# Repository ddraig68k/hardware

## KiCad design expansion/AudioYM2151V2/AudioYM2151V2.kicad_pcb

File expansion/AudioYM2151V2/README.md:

# YM2151 V2 Sound Card

This second version of the [YM2151 Sound Card](/YM2151-Sound/) extends the capabilites of the original. In addition to the YM2151, two Oki MSM6258 chips for dual ADPCM audio channels.

The 68008 memory map
| Device | Start Address | End Address |
|-|-|-|
| Static Ram    | 0x000000 | 0x07FFFF |
| ROM           | 0x100000 | 0x107FFF |
| STATUS_LATCH	| 0x200000 | 0x200000 |
| REG_LATCH	    | 0x200001 | 0x200001 |
| DATA_LATCH	| 0x200002 | 0x200002 |
| DUART	        | 0x200100 | 0x2001FF |
| YM2151	    | 0x200200 | 0x2002FF |
| MSM6295 1	    | 0x200300 | 0x2003FF |
| MSM6295 2	    | 0x200400 | 0x2004FF |

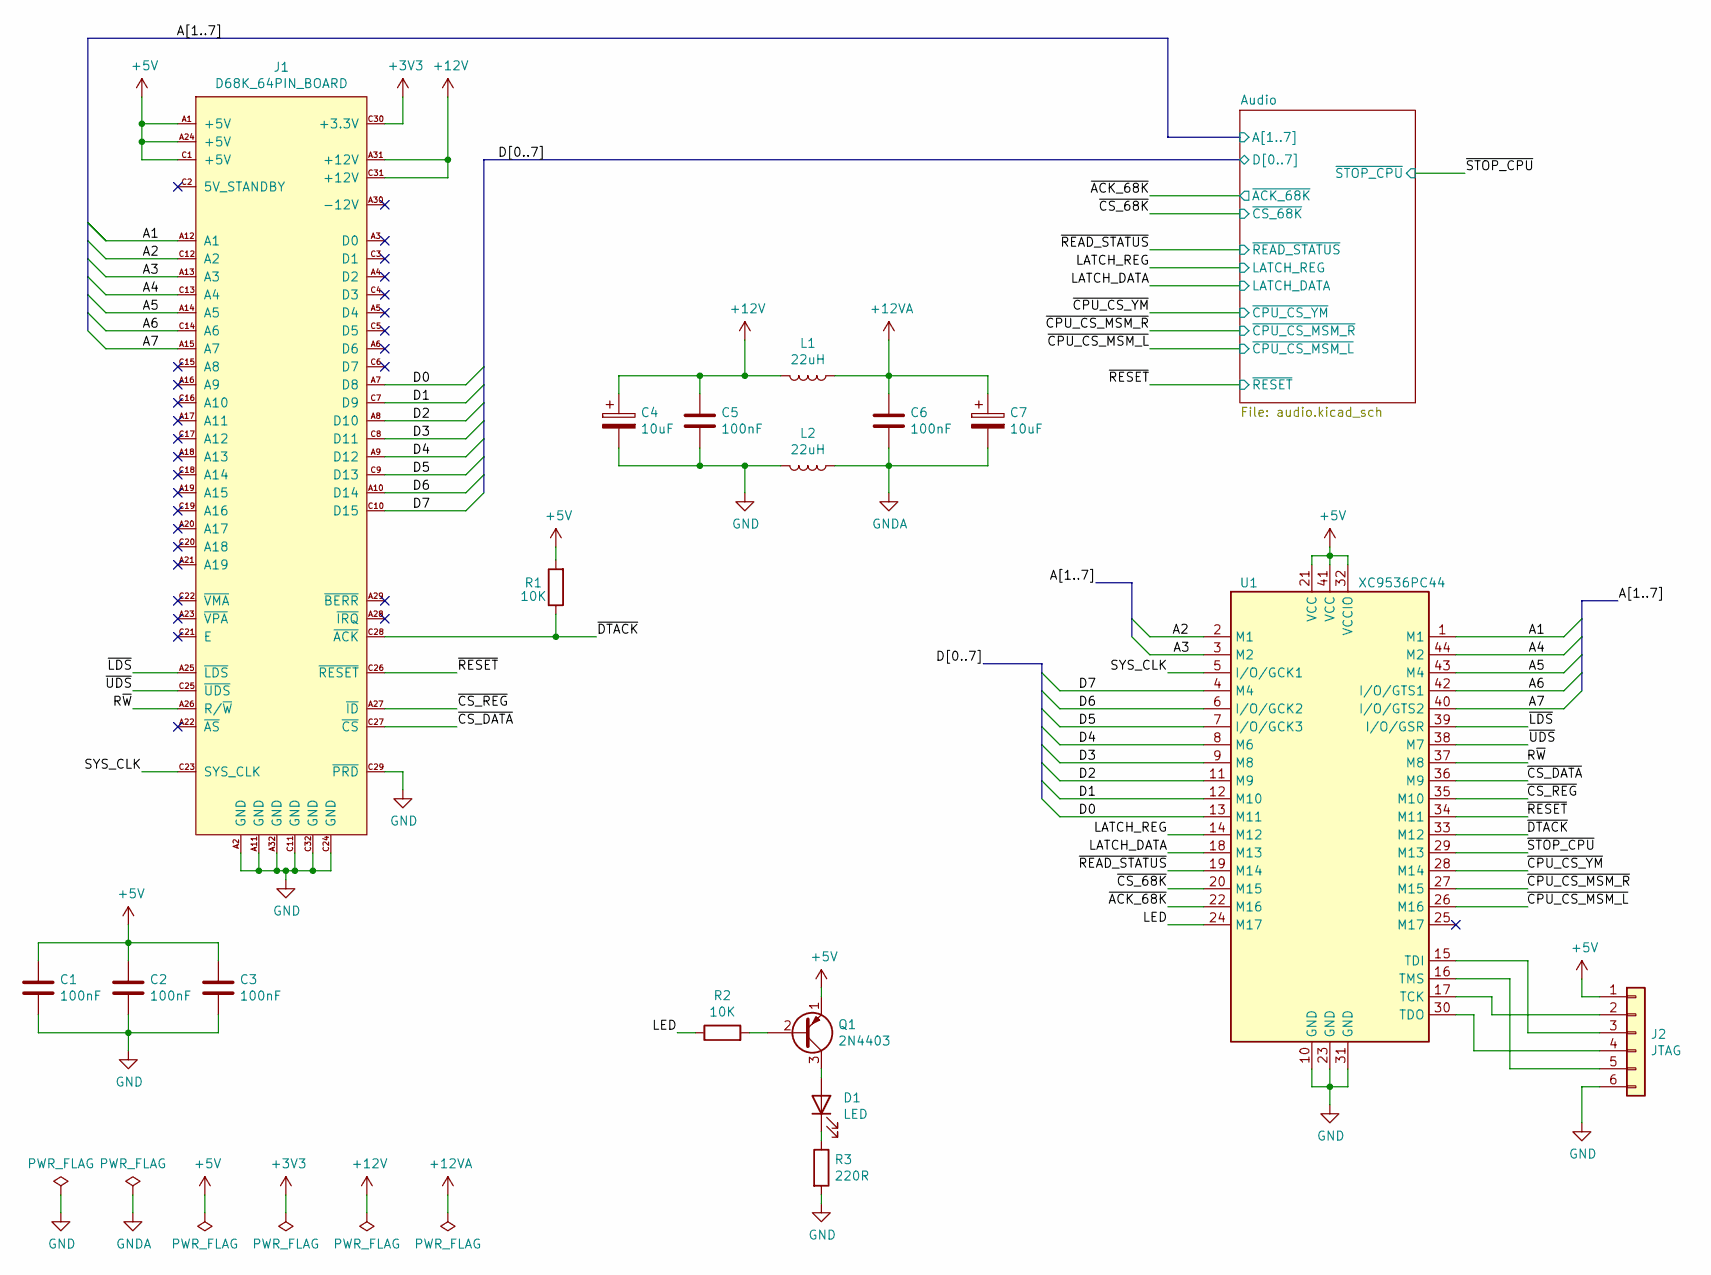
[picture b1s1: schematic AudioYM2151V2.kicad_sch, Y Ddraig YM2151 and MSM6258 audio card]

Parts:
C1, C2, C3, C5, C6: 100nF; C_Disc_D5.0mm_W2.5mm_P2.50mm
C4, C7: 10uF; CP_Radial_D5.0mm_P2.50mm
D1: LED; LED_D5.0mm
J1: D68K_64PIN_BOARD; DIN41612_C_2x32_Male_Horizontal_THT
J2: JTAG; PinHeader_1x06_P2.54mm_Vertical
L1, L2: 22uH; L_Radial_D8.7mm_P5.00mm_Fastron_07HCP
Q1: 2N4403; TO-92
R1, R2: 10K; R_Axial_DIN0207_L6.3mm_D2.5mm_P10.16mm_Horizontal
R3: 220R; R_Axial_DIN0207_L6.3mm_D2.5mm_P10.16mm_Horizontal
U1: XC9536PC44; PLCC-44_THT-Socket

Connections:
+3V3: J1.C30 (+3.3V)
+12V: C4.1, C5.1, J1.A31 (+12V), J1.C31 (+12V), L1.2
+12VA: C6.1, C7.1, L1.1; also elsewhere on the board
/A1: J1.A12 (A1), U1.1 (M1); also elsewhere on the board
/A2: J1.C12 (A2), U1.2 (M1); also elsewhere on the board
/A3: J1.A13 (A3), U1.3 (M2); also elsewhere on the board
/A4: J1.C13 (A4), U1.44 (M2); also elsewhere on the board
/A5: J1.A14 (A5), U1.43 (M4); also elsewhere on the board
/A6: J1.C14 (A6), U1.42 (I/O/GTS1); also elsewhere on the board
/A7: J1.A15 (A7), U1.40 (I/O/GTS2)
/D0: J1.A7 (D8), U1.13 (M11); also elsewhere on the board
/D1: J1.C7 (D9), U1.12 (M10); also elsewhere on the board
/D2: J1.A8 (D10), U1.11 (M9); also elsewhere on the board
/D3: J1.C8 (D11), U1.9 (M8); also elsewhere on the board
/D4: J1.A9 (D12), U1.8 (M6); also elsewhere on the board
/D5: J1.C9 (D13), U1.7 (I/O/GCK3); also elsewhere on the board
/D6: J1.A10 (D14), U1.6 (I/O/GCK2); also elsewhere on the board
/D7: J1.C10 (D15), U1.4 (M4); also elsewhere on the board
/LATCH_DATA: U1.18 (M13); also elsewhere on the board
/LATCH_REG: U1.14 (M12); also elsewhere on the board
/R~W: J1.A26 (R/~W), U1.37 (M8)
/SYS_CLK: J1.C23 (SYS_CLK), U1.5 (I/O/GCK1)
/~ACK_68K: U1.22 (M16); also elsewhere on the board
/~CPU_CS_MSM_L: U1.26 (M16); also elsewhere on the board
/~CPU_CS_MSM_R: U1.27 (M15); also elsewhere on the board
/~CPU_CS_YM: U1.28 (M14); also elsewhere on the board
/~CS_68K: U1.20 (M15); also elsewhere on the board
/~CS_DATA: J1.C27 (~CS), U1.36 (M9)
/~CS_REG: J1.A27 (~ID), U1.35 (M10)
/~DTACK: J1.C28 (~ACK), R1.1, U1.33 (M12)
/~LDS: J1.A25 (~LDS), U1.39 (I/O/GSR)
/~READ_STATUS: U1.19 (M14); also elsewhere on the board
/~RESET: J1.C26 (~RESET), U1.34 (M11); also elsewhere on the board
/~STOP_CPU: U1.29 (M13); also elsewhere on the board
/~UDS: J1.C25 (~UDS), U1.38 (M7)
GND: C1.2, C2.2, C3.2, C4.2, C5.2, J1.A2 (GND), J1.A11 (GND), J1.A32 (GND), J1.C11 (GND), J1.C24 (GND), J1.C29 (~PRD), J1.C32 (GND), J2.6, L2.2, R3.2, U1.10 (GND), U1.23 (GND), U1.31 (GND); also elsewhere on the board
GNDA: C6.2, C7.2, L2.1; also elsewhere on the board
unnamed: J2.2, U1.17 (TCK)
unnamed: J2.3, U1.15 (TDI)
unnamed: J2.4, U1.30 (TDO)
unnamed: J2.5, U1.16 (TMS)

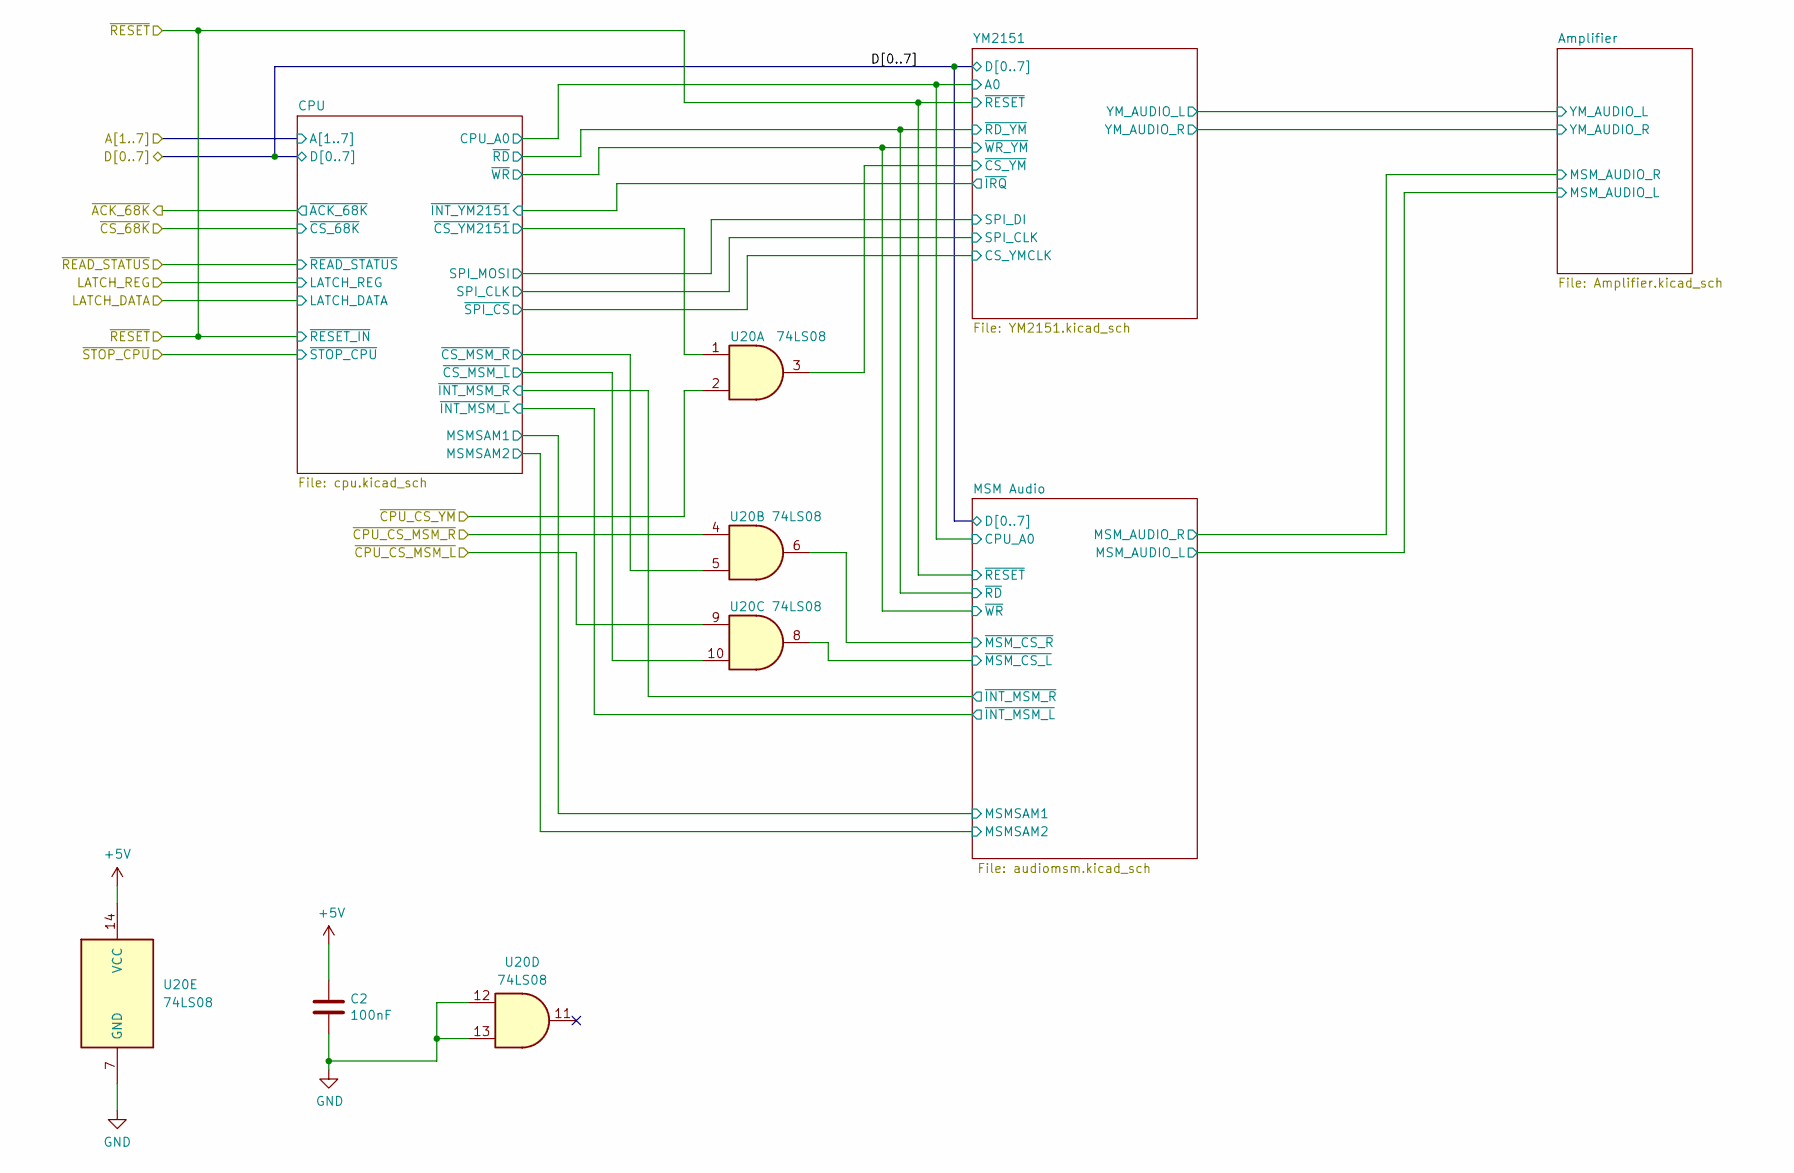
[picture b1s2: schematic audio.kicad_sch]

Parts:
C2: 100nF; C_Disc_D5.0mm_W2.5mm_P2.50mm
U20: 74LS08; DIP-14_W7.62mm_Socket

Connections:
/Audio/CPU/~CS_MSM_L: U20.10; also elsewhere on the board
/Audio/CPU/~CS_MSM_R: U20.5; also elsewhere on the board
/Audio/CPU/~CS_YM2151: U20.1; also elsewhere on the board
/Audio/MSM Audio/~MSM_CS_L: U20.8; also elsewhere on the board
/Audio/MSM Audio/~MSM_CS_R: U20.6; also elsewhere on the board
/Audio/YM2151/~CS_YM: U20.3; also elsewhere on the board
/~CPU_CS_MSM_L: U20.9; also elsewhere on the board
/~CPU_CS_MSM_R: U20.4; also elsewhere on the board
/~CPU_CS_YM: U20.2; also elsewhere on the board
GND: C2.2, U20.7 (GND), U20.12, U20.13; also elsewhere on the board

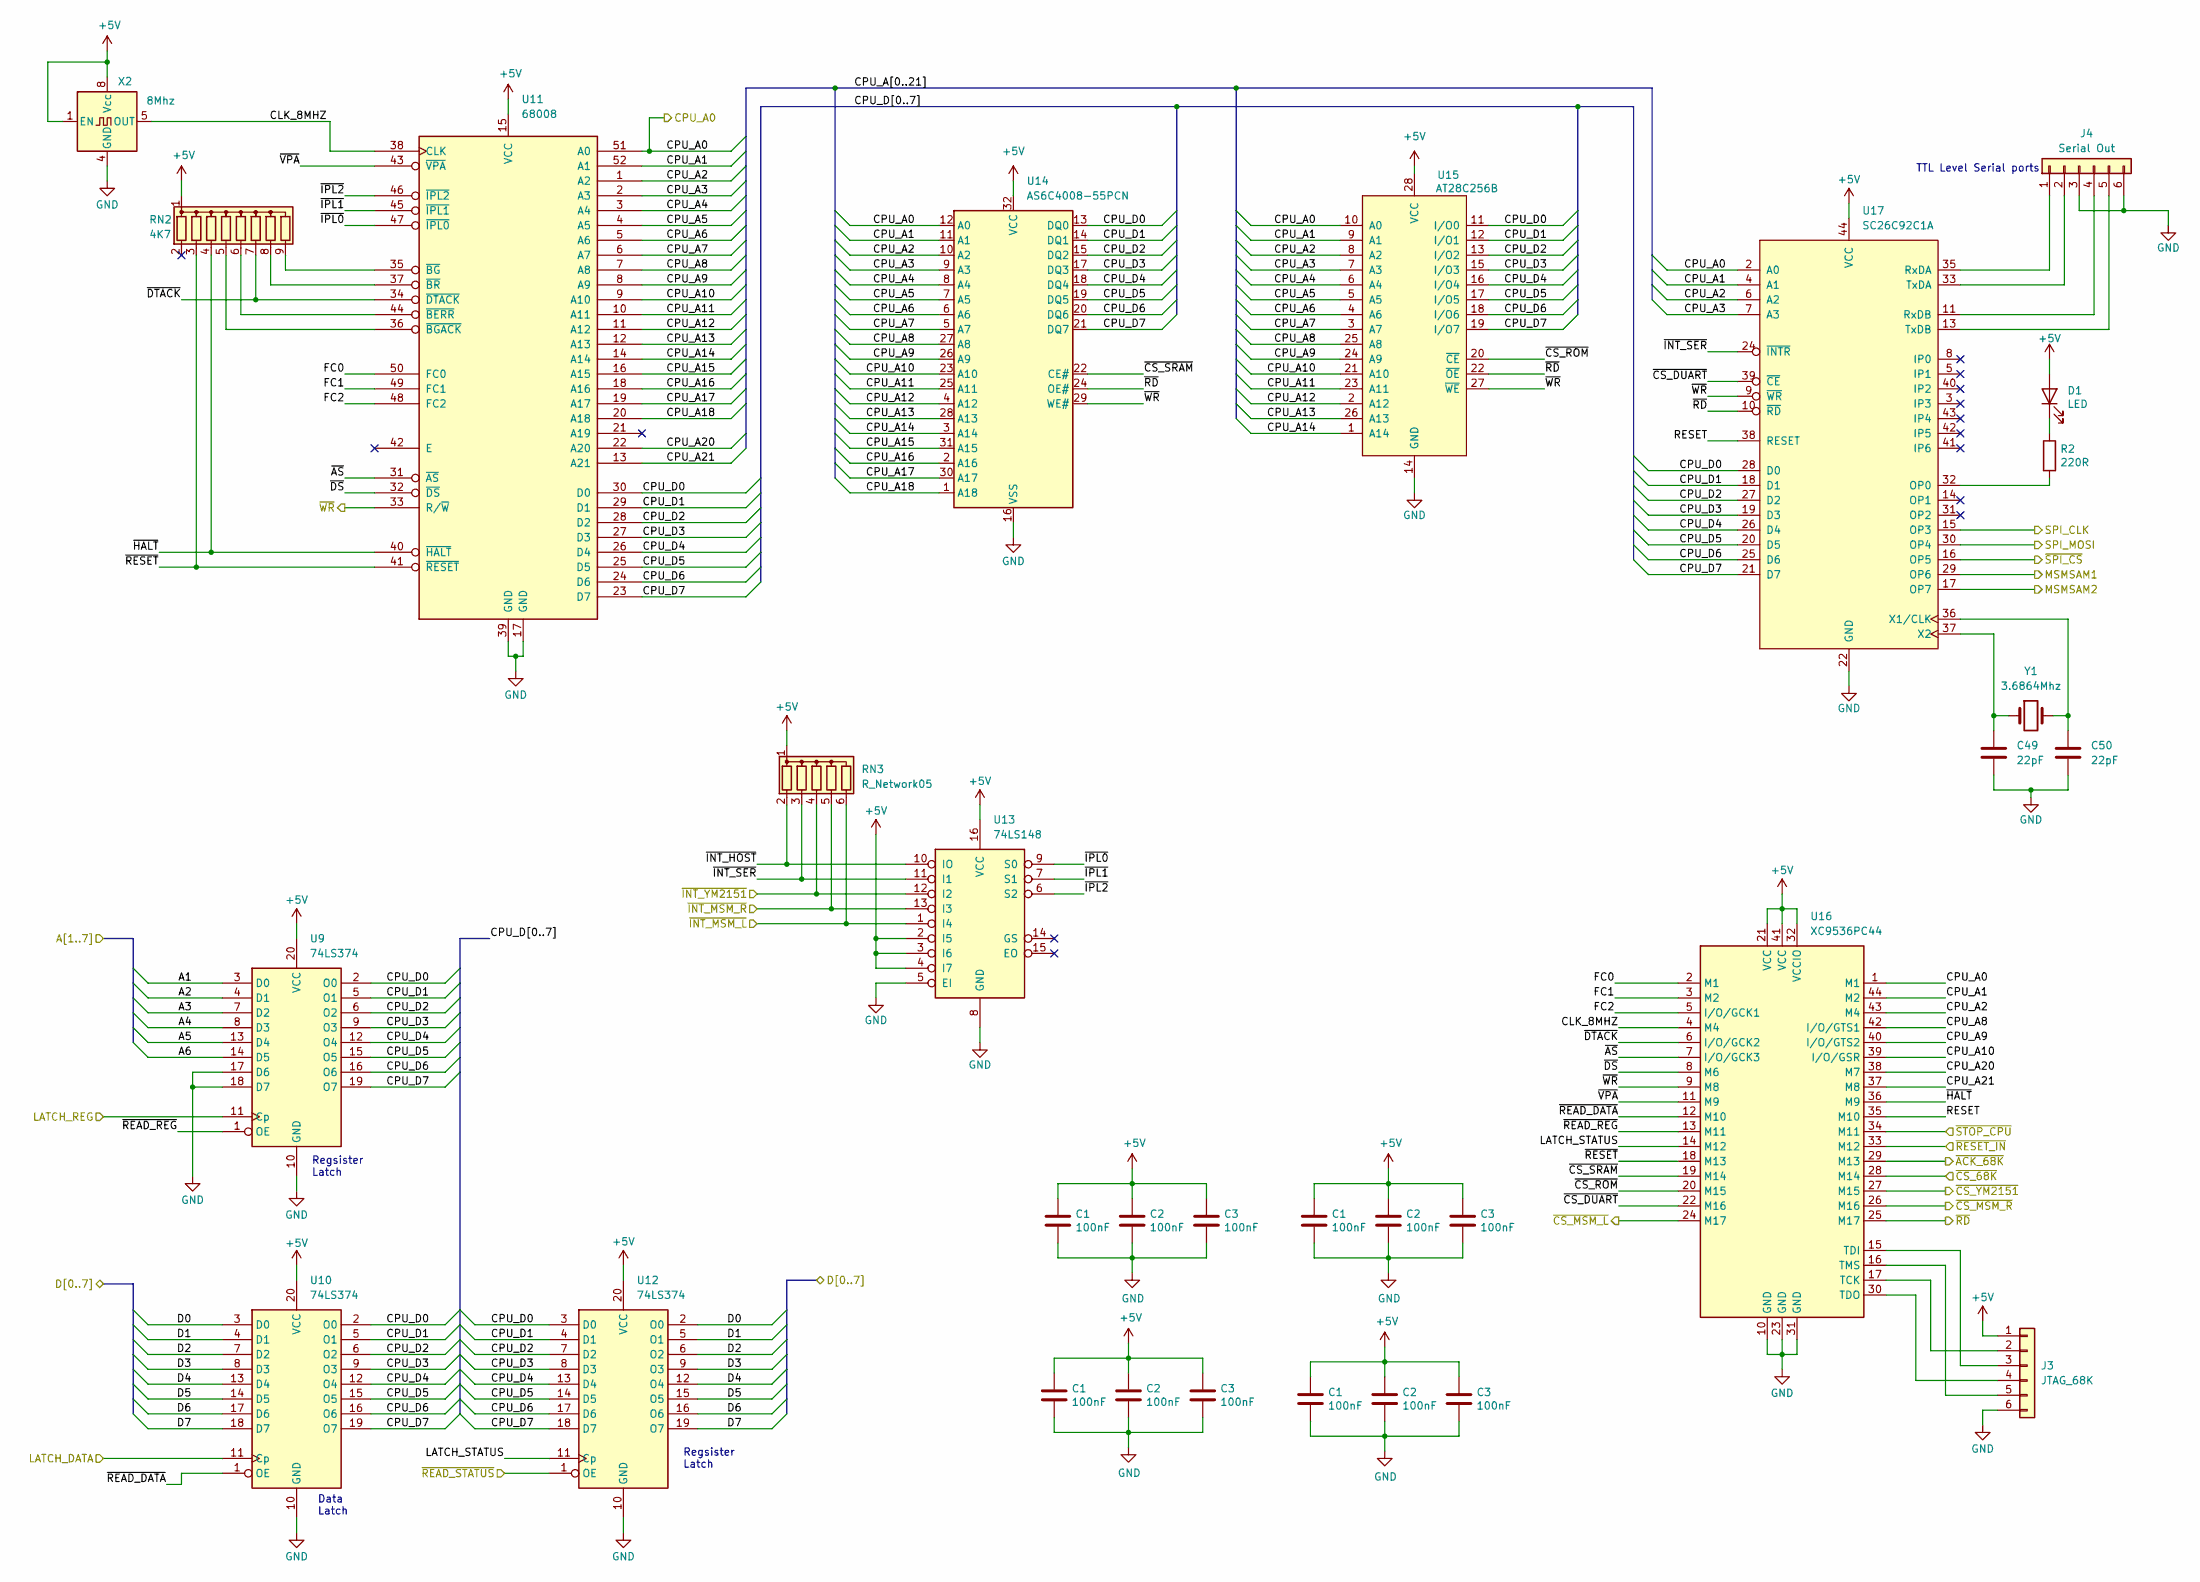
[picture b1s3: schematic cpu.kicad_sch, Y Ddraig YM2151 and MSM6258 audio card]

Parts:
C1, C2, C3: 100nF; C_Disc_D5.0mm_W2.5mm_P2.50mm
C49, C50: 22pF; C_Disc_D5.0mm_W2.5mm_P2.50mm
D1: LED; LED_D5.0mm
J3: JTAG_68K; PinHeader_1x06_P2.54mm_Vertical
J4: Serial Out; PinHeader_1x06_P2.54mm_Vertical
R2: 220R; R_Axial_DIN0207_L6.3mm_D2.5mm_P10.16mm_Horizontal
RN2: 4K7; R_Array_SIP9
RN3: R_Network05; R_Array_SIP6
U9, U10, U12: 74LS374; DIP-20_W7.62mm_Socket
U11: 68008; PLCC-52_THT-Socket
U13: 74LS148; DIP-16_W7.62mm_Socket
U14: AS6C4008-55PCN; DIP-32_W15.24mm
U15: AT28C256B; DIP-28_W15.24mm_Socket
U16: XC9536PC44; PLCC-44_THT-Socket
U17: SC26C92C1A; PLCC-44_THT-Socket
X2: 8Mhz; Oscillator_DIP-8
Y1: 3.6864Mhz; Crystal_HC18-U_Vertical

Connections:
/A1: U9.3 (D0); also elsewhere on the board
/A2: U9.4 (D1); also elsewhere on the board
/A3: U9.7 (D2); also elsewhere on the board
/A4: U9.8 (D3); also elsewhere on the board
/A5: U9.13 (D4); also elsewhere on the board
/A6: U9.14 (D5); also elsewhere on the board
/Audio/CPU/CLK_8MHZ: U11.38 (CLK), U16.4 (M4), X2.5 (OUT)
/Audio/CPU/CPU_A0: U11.51 (A0), U14.12 (A0), U15.10 (A0), U16.1 (M1), U17.2 (A0); also elsewhere on the board
/Audio/CPU/CPU_A1: U11.52 (A1), U14.11 (A1), U15.9 (A1), U16.44 (M2), U17.4 (A1)
/Audio/CPU/CPU_A2: U11.1 (A2), U14.10 (A2), U15.8 (A2), U16.43 (M4), U17.6 (A2)
/Audio/CPU/CPU_A3: U11.2 (A3), U14.9 (A3), U15.7 (A3), U17.7 (A3)
/Audio/CPU/CPU_A4: U11.3 (A4), U14.8 (A4), U15.6 (A4)
/Audio/CPU/CPU_A5: U11.4 (A5), U14.7 (A5), U15.5 (A5)
/Audio/CPU/CPU_A6: U11.5 (A6), U14.6 (A6), U15.4 (A6)
/Audio/CPU/CPU_A7: U11.6 (A7), U14.5 (A7), U15.3 (A7)
/Audio/CPU/CPU_A8: U11.7 (A8), U14.27 (A8), U15.25 (A8), U16.42 (I/O/GTS1)
/Audio/CPU/CPU_A9: U11.8 (A9), U14.26 (A9), U15.24 (A9), U16.40 (I/O/GTS2)
/Audio/CPU/CPU_A10: U11.9 (A10), U14.23 (A10), U15.21 (A10), U16.39 (I/O/GSR)
/Audio/CPU/CPU_A11: U11.10 (A11), U14.25 (A11), U15.23 (A11)
/Audio/CPU/CPU_A12: U11.11 (A12), U14.4 (A12), U15.2 (A12)
/Audio/CPU/CPU_A13: U11.12 (A13), U14.28 (A13), U15.26 (A13)
/Audio/CPU/CPU_A14: U11.14 (A14), U14.3 (A14), U15.1 (A14)
/Audio/CPU/CPU_A15: U11.16 (A15), U14.31 (A15)
/Audio/CPU/CPU_A16: U11.18 (A16), U14.2 (A16)
/Audio/CPU/CPU_A17: U11.19 (A17), U14.30 (A17)
/Audio/CPU/CPU_A18: U11.20 (A18), U14.1 (A18)
/Audio/CPU/CPU_A20: U11.22 (A20), U16.38 (M7)
/Audio/CPU/CPU_A21: U11.13 (A21), U16.37 (M8)
/Audio/CPU/CPU_D0: U9.2 (O0), U10.2 (O0), U11.30 (D0), U12.3 (D0), U14.13 (DQ0), U15.11 (I/O0), U17.28 (D0)
/Audio/CPU/CPU_D1: U9.5 (O1), U10.5 (O1), U11.29 (D1), U12.4 (D1), U14.14 (DQ1), U15.12 (I/O1), U17.18 (D1)
/Audio/CPU/CPU_D2: U9.6 (O2), U10.6 (O2), U11.28 (D2), U12.7 (D2), U14.15 (DQ2), U15.13 (I/O2), U17.27 (D2)
/Audio/CPU/CPU_D3: U9.9 (O3), U10.9 (O3), U11.27 (D3), U12.8 (D3), U14.17 (DQ3), U15.15 (I/O3), U17.19 (D3)
/Audio/CPU/CPU_D4: U9.12 (O4), U10.12 (O4), U11.26 (D4), U12.13 (D4), U14.18 (DQ4), U15.16 (I/O4), U17.26 (D4)
/Audio/CPU/CPU_D5: U9.15 (O5), U10.15 (O5), U11.25 (D5), U12.14 (D5), U14.19 (DQ5), U15.17 (I/O5), U17.20 (D5)
/Audio/CPU/CPU_D6: U9.16 (O6), U10.16 (O6), U11.24 (D6), U12.17 (D6), U14.20 (DQ6), U15.18 (I/O6), U17.25 (D6)
/Audio/CPU/CPU_D7: U9.19 (O7), U10.19 (O7), U11.23 (D7), U12.18 (D7), U14.21 (DQ7), U15.19 (I/O7), U17.21 (D7)
/Audio/CPU/FC0: U11.50 (FC0), U16.2 (M1)
/Audio/CPU/FC1: U11.49 (FC1), U16.3 (M2)
/Audio/CPU/FC2: U11.48 (FC2), U16.5 (I/O/GCK1)
/Audio/CPU/LATCH_STATUS: U12.11 (Cp), U16.14 (M12)
/Audio/CPU/MSMSAM1: U17.29 (OP6); also elsewhere on the board
/Audio/CPU/MSMSAM2: U17.17 (OP7); also elsewhere on the board
/Audio/CPU/RESET: U16.35 (M10), U17.38 (RESET)
/Audio/CPU/SPI_CLK: U17.15 (OP3); also elsewhere on the board
/Audio/CPU/SPI_MOSI: U17.30 (OP4); also elsewhere on the board
/Audio/CPU/~AS: U11.31 (~AS), U16.7 (I/O/GCK3)
/Audio/CPU/~CS_DUART: U16.22 (M16), U17.39 (~CE)
/Audio/CPU/~CS_MSM_L: U16.24 (M17); also elsewhere on the board
/Audio/CPU/~CS_MSM_R: U16.26 (M16); also elsewhere on the board
/Audio/CPU/~CS_ROM: U15.20 (~CE), U16.20 (M15)
/Audio/CPU/~CS_SRAM: U14.22 (CE#), U16.19 (M14)
/Audio/CPU/~CS_YM2151: U16.27 (M15); also elsewhere on the board
/Audio/CPU/~DS: U11.32 (~DS), U16.8 (M6)
/Audio/CPU/~DTACK: RN2.7 (R6), U11.34 (~DTACK), U16.6 (I/O/GCK2)
/Audio/CPU/~HALT: RN2.4 (R3), U11.40 (~HALT), U16.36 (M9)
/Audio/CPU/~INT_HOST: RN3.2 (R1), U13.10 (IO)
/Audio/CPU/~INT_MSM_L: RN3.6 (R5), U13.1 (I4); also elsewhere on the board
/Audio/CPU/~INT_MSM_R: RN3.5 (R4), U13.13 (I3); also elsewhere on the board
/Audio/CPU/~INT_SER: RN3.3 (R2), U13.11 (I1), U17.24 (~INTR)
/Audio/CPU/~INT_YM2151: RN3.4 (R3), U13.12 (I2); also elsewhere on the board
/Audio/CPU/~IPL0: U11.47 (~IPL0), U13.9 (S0)
/Audio/CPU/~IPL1: U11.45 (~IPL1), U13.7 (S1)
/Audio/CPU/~IPL2: U11.46 (~IPL2), U13.6 (S2)
/Audio/CPU/~RD: U14.24 (OE#), U15.22 (~OE), U16.25 (M17), U17.10 (~RD); also elsewhere on the board
/Audio/CPU/~READ_DATA: U10.1 (OE), U16.12 (M10)
/Audio/CPU/~READ_REG: U9.1 (OE), U16.13 (M11)
/Audio/CPU/~RESET: RN2.3 (R2), U11.41 (~RESET), U16.18 (M13)
/Audio/CPU/~SPI_CS: U17.16 (OP5); also elsewhere on the board
/Audio/CPU/~VPA: U11.43 (~VPA), U16.11 (M9)
/Audio/CPU/~WR: U11.33 (R/~W), U14.29 (WE#), U15.27 (~WE), U16.9 (M8), U17.9 (~WR); also elsewhere on the board
/D0: U10.3 (D0), U12.2 (O0); also elsewhere on the board
/D1: U10.4 (D1), U12.5 (O1); also elsewhere on the board
/D2: U10.7 (D2), U12.6 (O2); also elsewhere on the board
/D3: U10.8 (D3), U12.9 (O3); also elsewhere on the board
/D4: U10.13 (D4), U12.12 (O4); also elsewhere on the board
/D5: U10.14 (D5), U12.15 (O5); also elsewhere on the board
/D6: U10.17 (D6), U12.16 (O6); also elsewhere on the board
/D7: U10.18 (D7), U12.19 (O7); also elsewhere on the board
/LATCH_DATA: U10.11 (Cp); also elsewhere on the board
/LATCH_REG: U9.11 (Cp); also elsewhere on the board
/~ACK_68K: U16.29 (M13); also elsewhere on the board
/~CS_68K: U16.28 (M14); also elsewhere on the board
/~READ_STATUS: U12.1 (OE); also elsewhere on the board
/~RESET: U16.33 (M12); also elsewhere on the board
/~STOP_CPU: U16.34 (M11); also elsewhere on the board
GND: C1.2, C2.2, C3.2, C49.2, C50.2, J3.6, J4.3, J4.6, U9.10 (GND), U9.17 (D6), U9.18 (D7), U10.10 (GND), U11.17 (GND), U11.39 (GND), U12.10 (GND), U13.5 (EI), U13.8 (GND), U14.16 (VSS), U15.14 (GND), U16.10 (GND), U16.23 (GND), U16.31 (GND), U17.22 (GND), X2.4 (GND); also elsewhere on the board
unnamed: J3.2, U16.17 (TCK)
unnamed: J3.3, U16.15 (TDI)
unnamed: J3.4, U16.30 (TDO)
unnamed: J3.5, U16.16 (TMS)
unnamed: J4.1, U17.35 (RxDA)
unnamed: J4.2, U17.33 (TxDA)
unnamed: J4.4, U17.11 (RxDB)
unnamed: J4.5, U17.13 (TxDB)
unnamed: RN2.5 (R4), U11.36 (~BGACK)
unnamed: RN2.6 (R5), U11.44 (~BERR)
unnamed: RN2.8 (R7), U11.37 (~BR)
unnamed: RN2.9 (R8), U11.35 (~BG)
unnamed: C50.1, U17.36 (X1/CLK), Y1.2
unnamed: C49.1, U17.37 (X2), Y1.1

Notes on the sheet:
Regsister Latch
Data Latch
TTL Level Serial ports

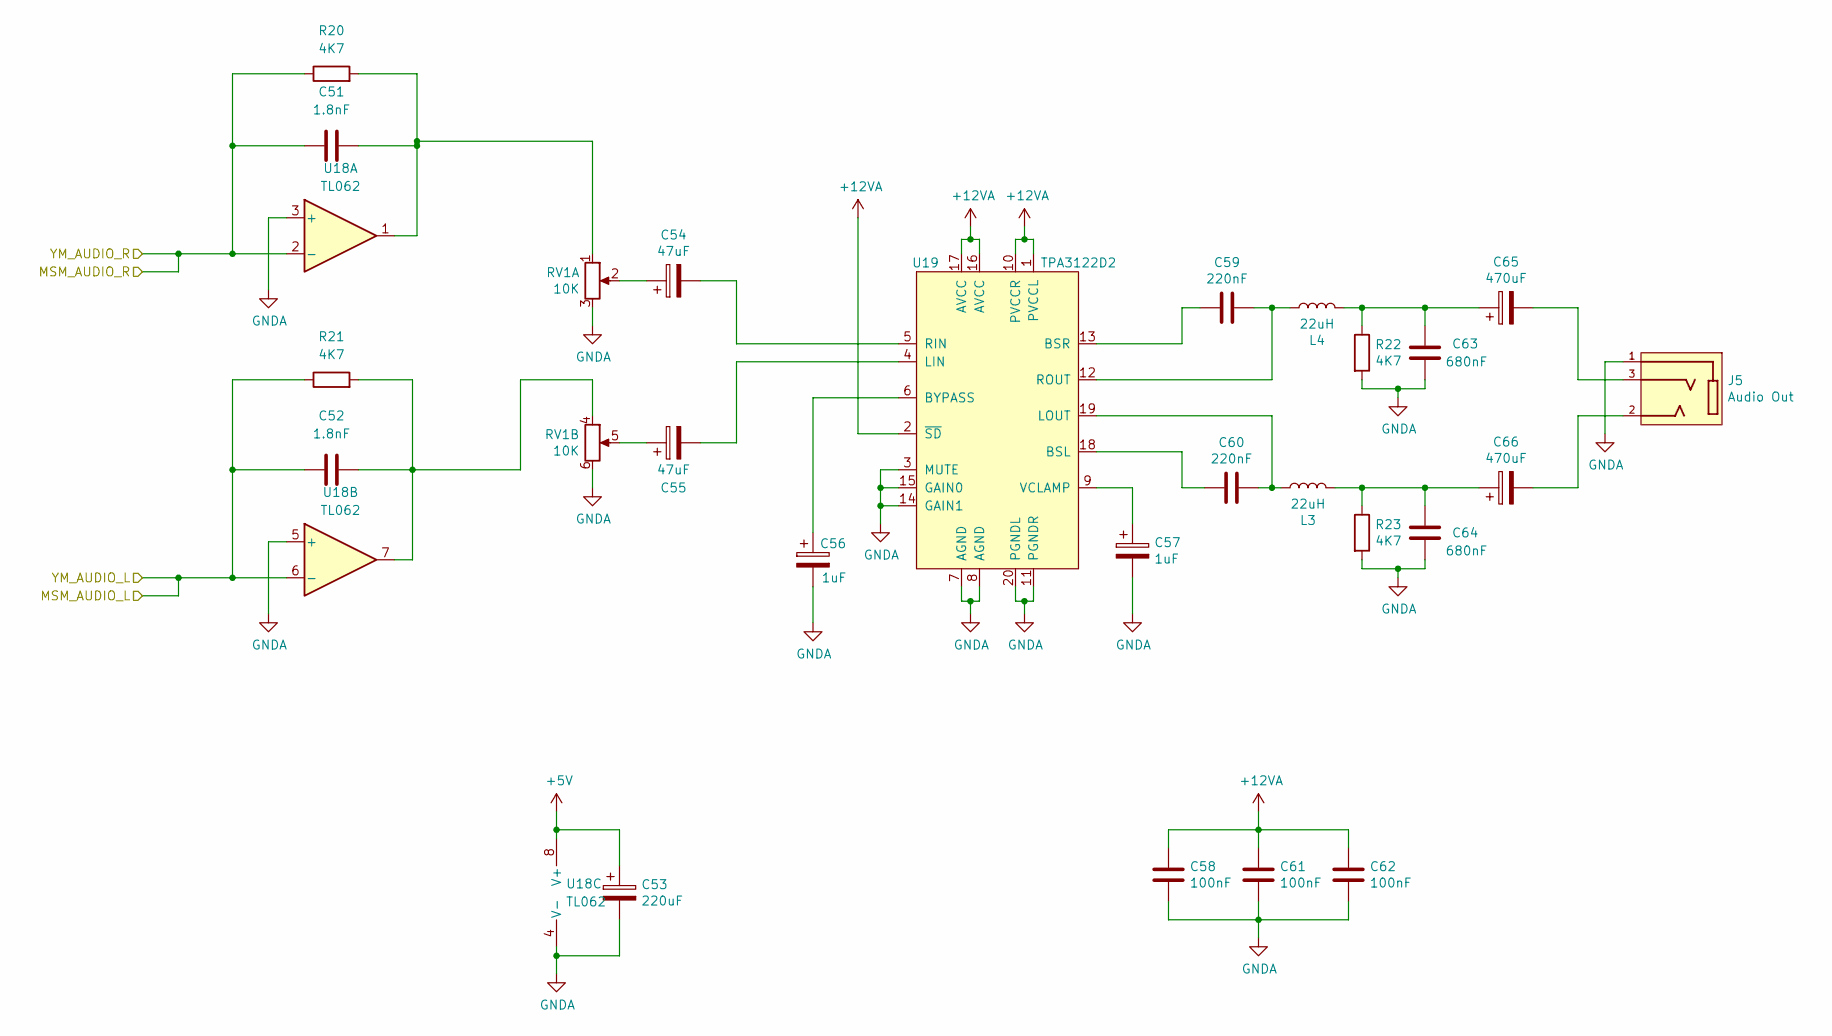
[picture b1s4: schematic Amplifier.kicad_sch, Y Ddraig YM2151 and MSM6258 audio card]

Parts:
C51, C52: 1.8nF; C_Disc_D5.0mm_W2.5mm_P2.50mm
C53: 220uF; CP_Radial_D5.0mm_P2.50mm
C54, C55: 47uF; CP_Radial_D5.0mm_P2.50mm
C56, C57: 1uF; CP_Radial_D5.0mm_P2.50mm
C58, C61, C62: 100nF; C_Disc_D5.0mm_W2.5mm_P2.50mm
C59, C60: 220nF; C_Disc_D5.0mm_W2.5mm_P2.50mm
C63, C64: 680nF; C_Disc_D5.0mm_W2.5mm_P2.50mm
C65, C66: 470uF; CP_Radial_D5.0mm_P2.50mm
J5: Audio Out; SWITCHCRAFT_35RAPC2BHN2; PARTREV L
L3, L4: 22uH; L_Radial_D8.7mm_P5.00mm_Fastron_07HCP
R20, R21, R22, R23: 4K7; R_Axial_DIN0207_L6.3mm_D2.5mm_P10.16mm_Horizontal
RV1: 10K; Potentiometer_Alps_RK163_Dual_Horizontal
U18: TL062; DIP-8_W7.62mm_Socket
U19: TPA3122D2; DIP-20_W7.62mm_Socket

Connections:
+12VA: C58.1, C61.1, C62.1, U19.1 (PVCCL), U19.2 (~SD), U19.10 (PVCCR), U19.16 (AVCC), U19.17 (AVCC); also elsewhere on the board
/Audio/Amplifier/MSM_AUDIO_L: C52.1, R21.1, U18.6 (-); also elsewhere on the board
/Audio/Amplifier/MSM_AUDIO_R: C51.1, R20.1, U18.2 (-); also elsewhere on the board
GNDA: C53.2, C56.2, C57.2, C58.2, C61.2, C62.2, C63.1, C64.1, J5.1, R22.2, R23.2, RV1.3, RV1.6, U18.3 (+), U18.4 (V-), U18.5 (+), U19.3 (MUTE), U19.7 (AGND), U19.8 (AGND), U19.11 (PGNDR), U19.14 (GAIN1), U19.15 (GAIN0), U19.20 (PGNDL); also elsewhere on the board
unnamed: C51.2, R20.2, RV1.1, U18.1
unnamed: C52.2, R21.2, RV1.4, U18.7
unnamed: C54.1, RV1.2
unnamed: C55.1, RV1.5
unnamed: C63.2, C65.1, L4.2, R22.1
unnamed: C64.2, C66.1, L3.2, R23.1
unnamed: C65.2, J5.3
unnamed: C66.2, J5.2
unnamed: C60.2, U19.18 (BSL)
unnamed: C59.2, U19.13 (BSR)
unnamed: C56.1, U19.6 (BYPASS)
unnamed: C55.2, U19.4 (LIN)
unnamed: C60.1, L3.1, U19.19 (LOUT)
unnamed: C54.2, U19.5 (RIN)
unnamed: C59.1, L4.1, U19.12 (ROUT)
unnamed: C57.1, U19.9 (VCLAMP)

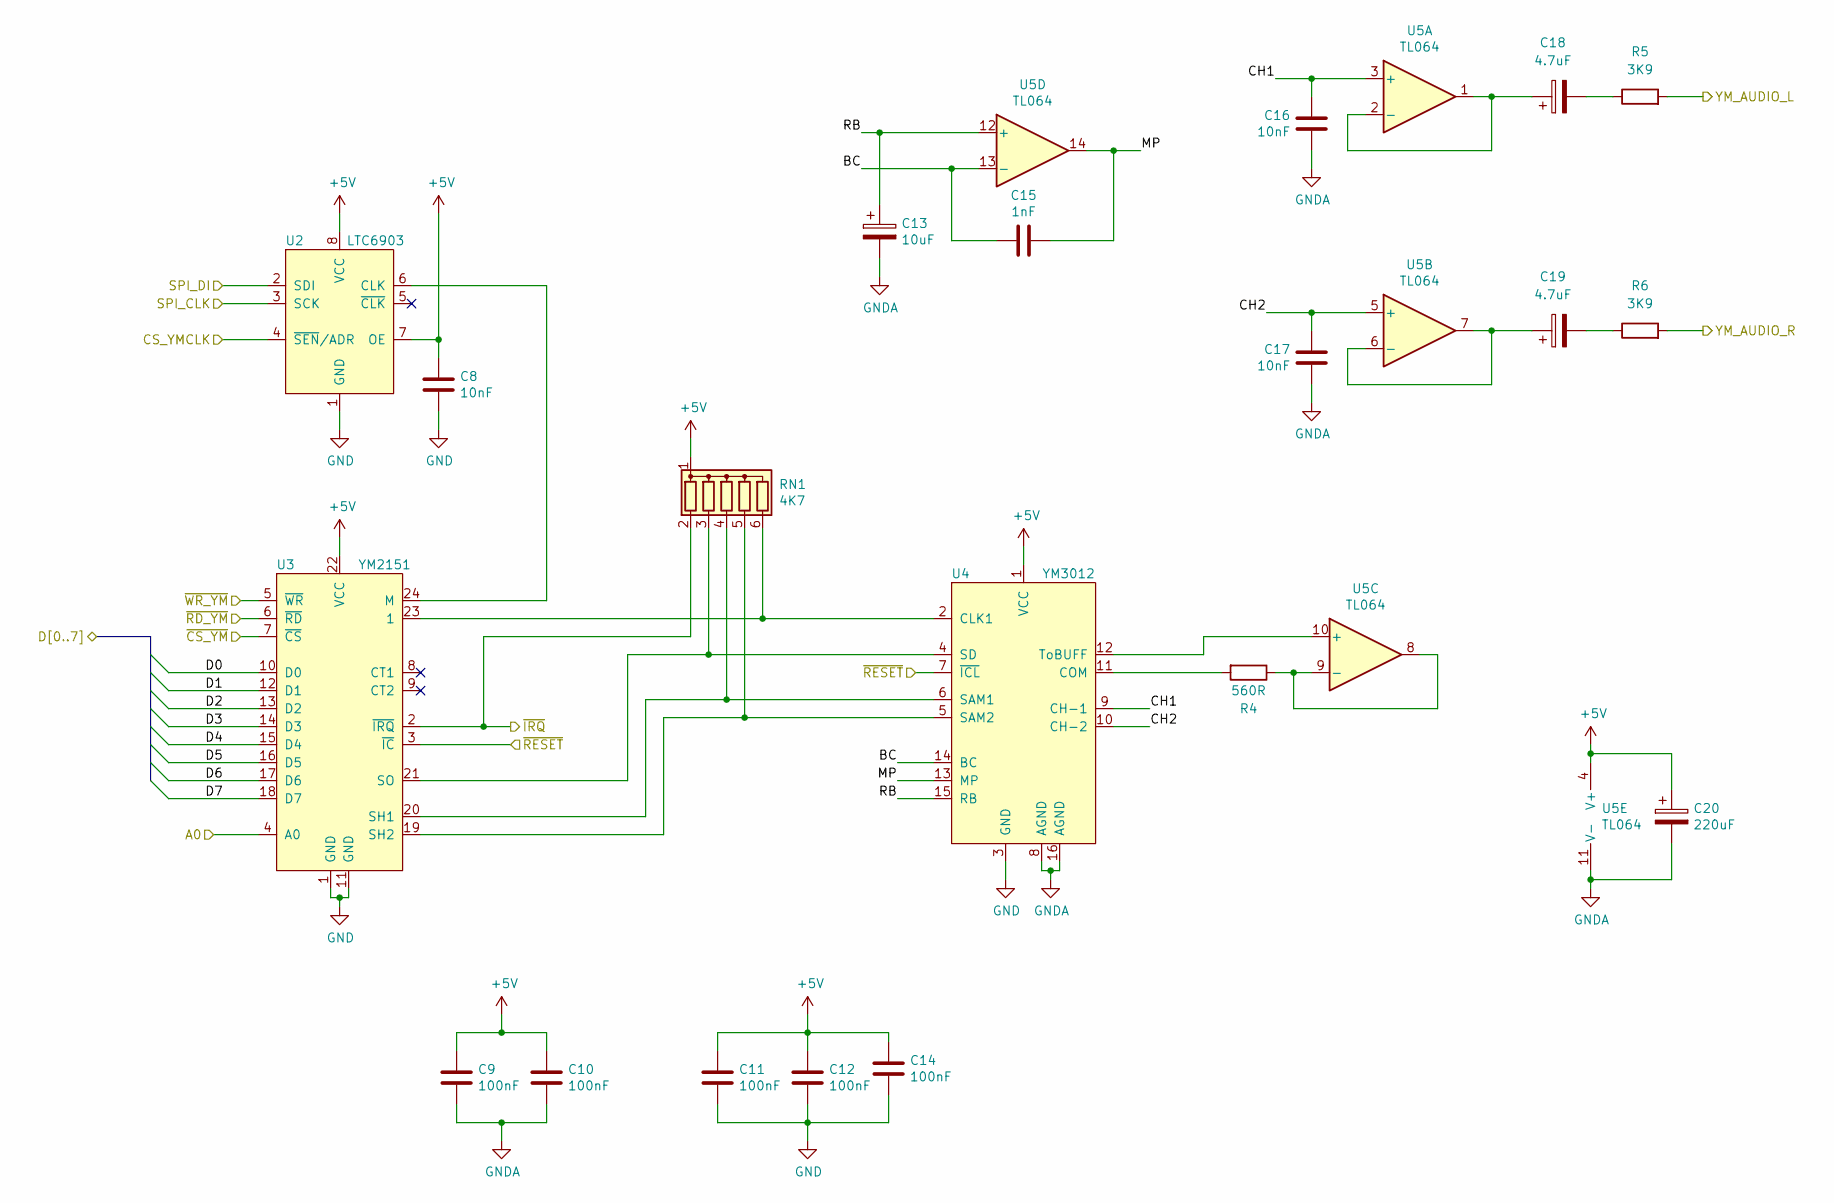
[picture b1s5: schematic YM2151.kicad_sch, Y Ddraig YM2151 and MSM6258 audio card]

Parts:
C8, C16, C17: 10nF; C_Disc_D5.0mm_W2.5mm_P2.50mm
C9, C10, C11, C12, C14: 100nF; C_Disc_D5.0mm_W2.5mm_P2.50mm
C13: 10uF; CP_Radial_D5.0mm_P2.50mm
C15: 1nF; C_Disc_D5.0mm_W2.5mm_P2.50mm
C18, C19: 4.7uF; CP_Radial_D5.0mm_P2.50mm
C20: 220uF; CP_Radial_D5.0mm_P2.50mm
R4: 560R; R_Axial_DIN0207_L6.3mm_D2.5mm_P10.16mm_Horizontal
R5, R6: 3K9; R_Axial_DIN0207_L6.3mm_D2.5mm_P10.16mm_Horizontal
RN1: 4K7; R_Array_SIP6
U2: LTC6903; MSOP-8_3x3mm_P0.65mm
U3: YM2151; DIP-24_W15.24mm
U4: YM3012; DIP-16_W7.62mm_Socket
U5: TL064; DIP-14_W7.62mm_Socket

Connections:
/Audio/Amplifier/MSM_AUDIO_L: R5.2; also elsewhere on the board
/Audio/Amplifier/MSM_AUDIO_R: R6.2; also elsewhere on the board
/Audio/CPU/CPU_A0: U3.4 (A0); also elsewhere on the board
/Audio/CPU/SPI_CLK: U2.3 (SCK); also elsewhere on the board
/Audio/CPU/SPI_MOSI: U2.2 (SDI); also elsewhere on the board
/Audio/CPU/~INT_YM2151: RN1.2 (R1), U3.2 (~IRQ); also elsewhere on the board
/Audio/CPU/~RD: U3.6 (~RD); also elsewhere on the board
/Audio/CPU/~SPI_CS: U2.4 (~SEN/ADR); also elsewhere on the board
/Audio/CPU/~WR: U3.5 (~WR); also elsewhere on the board
/Audio/YM2151/BC: C15.2, U4.14 (BC), U5.13 (-)
/Audio/YM2151/CH1: C16.2, U4.9 (CH-1), U5.3 (+)
/Audio/YM2151/CH2: C17.2, U4.10 (CH-2), U5.5 (+)
/Audio/YM2151/MP: C15.1, U4.13 (MP), U5.14
/Audio/YM2151/RB: C13.1, U4.15 (RB), U5.12 (+)
/Audio/YM2151/~CS_YM: U3.7 (~CS); also elsewhere on the board
/D0: U3.10 (D0); also elsewhere on the board
/D1: U3.12 (D1); also elsewhere on the board
/D2: U3.13 (D2); also elsewhere on the board
/D3: U3.14 (D3); also elsewhere on the board
/D4: U3.15 (D4); also elsewhere on the board
/D5: U3.16 (D5); also elsewhere on the board
/D6: U3.17 (D6); also elsewhere on the board
/D7: U3.18 (D7); also elsewhere on the board
/~RESET: U3.3 (~IC), U4.7 (~ICL); also elsewhere on the board
GND: C8.2, C11.2, C12.2, C14.2, U2.1 (GND), U3.1 (GND), U3.11 (GND), U4.3 (GND); also elsewhere on the board
GNDA: C9.2, C10.2, C13.2, C16.1, C17.1, C20.2, U4.8 (AGND), U4.16 (AGND), U5.11 (V-); also elsewhere on the board
unnamed: C18.2, R5.1
unnamed: C19.2, R6.1
unnamed: RN1.3 (R2), U3.21 (SO), U4.4 (SD)
unnamed: RN1.4 (R3), U3.20 (SH1), U4.6 (SAM1)
unnamed: RN1.5 (R4), U3.19 (SH2), U4.5 (SAM2)
unnamed: RN1.6 (R5), U3.23 (1), U4.2 (CLK1)
unnamed: U2.6 (CLK), U3.24 (M)
unnamed: R4.2, U4.11 (COM)
unnamed: U4.12 (ToBUFF), U5.10 (+)
unnamed: C18.1, U5.1, U5.2 (-)
unnamed: C19.1, U5.6 (-), U5.7
unnamed: R4.1, U5.8, U5.9 (-)

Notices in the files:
expansion/AudioYM2151V2/AudioYM2151V2.kicad_pcb:
© 2024 Stephen Moody
expansion/AudioYM2610/AudioYM2610.kicad_pcb:
© 2021 Stephen Moody
